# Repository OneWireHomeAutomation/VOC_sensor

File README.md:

# VOC_sensor
a one wire VOC sensor

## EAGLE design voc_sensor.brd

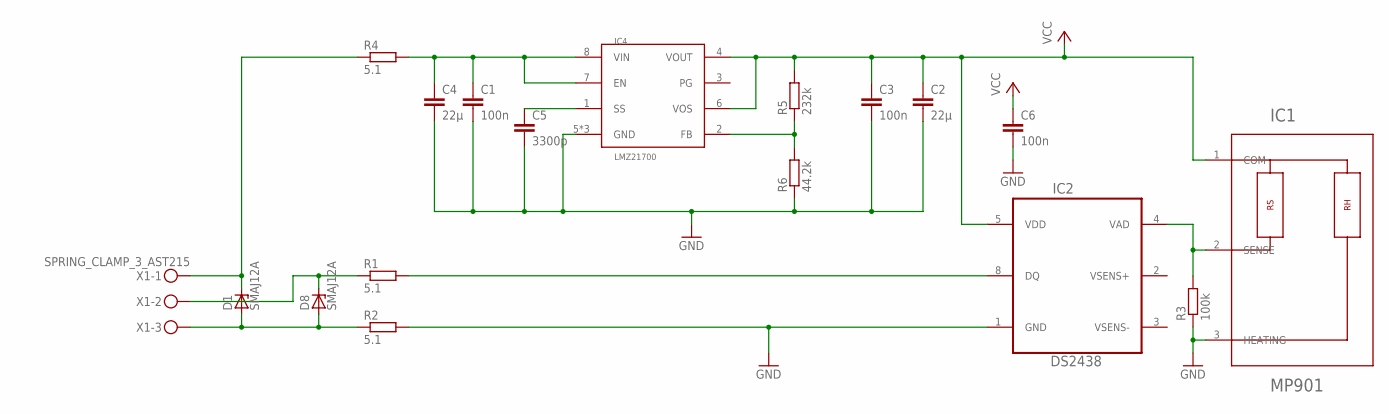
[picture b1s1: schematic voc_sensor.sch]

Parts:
C1: 100n; C0402; VOLTAGE >=25 V
C2: 22µ; C0805K; VOLTAGE >=6.3 V
C3, C6: 100n; C0402; VOLTAGE >=6.3 V
C4: 22µ; C0805K; VOLTAGE >=25 V
C5: 3300p; C0402; VOLTAGE >=25 V
D1, D8: SMAJ12A; DO214AC
IC1: MP901
IC2: DS2438; SO-08
IC4: LMZ21700
R1, R2, R4: 5.1; R0402
R3: 100k; R0402
R5: 232k; R0402
R6: 44.2k; R0402
X1: SPRING_CLAMP_3_AST215; AST215_3

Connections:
GND: C1.2, C2.2, C3.2, C4.2, C5.2, C6.2, IC1.3 (HEATING), IC2.1 (GND), IC4.5 (GND), IC4.TPAD@1 (GND), IC4.TPAD@2 (GND), R2.2, R3.1, R6.1
unnamed: IC1.2 (SENSE), IC2.4 (VAD), R3.2
unnamed: C1.1, C4.1, IC4.7 (EN), IC4.8 (VIN), R4.2
unnamed: D1.C, R4.1, X1.1A, X1.1B
unnamed: D1.A, D8.A, R2.1, X1.3A, X1.3B
unnamed: C5.1, IC4.1 (SS)
unnamed: IC4.2 (FB), R5.1, R6.2
unnamed: D8.C, R1.1, X1.2A, X1.2B
unnamed: IC2.8 (DQ), R1.2
VCC: C2.1, C3.1, C6.1, IC1.1 (COM), IC2.5 (VDD), IC4.4 (VOUT), IC4.6 (VOS), R5.2

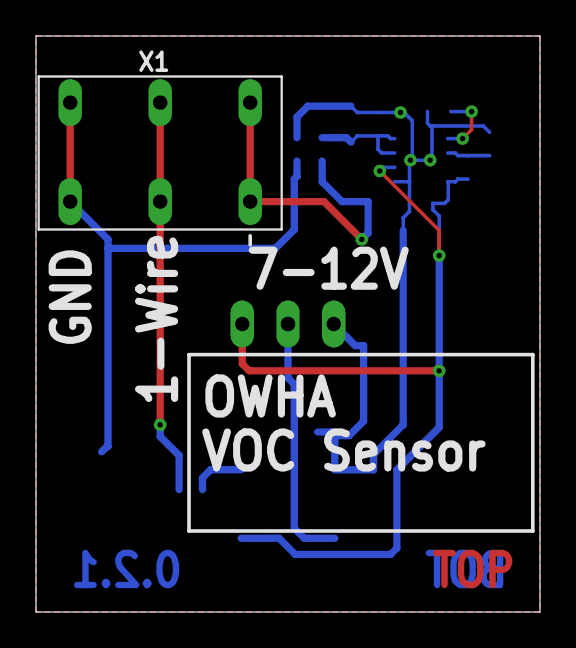
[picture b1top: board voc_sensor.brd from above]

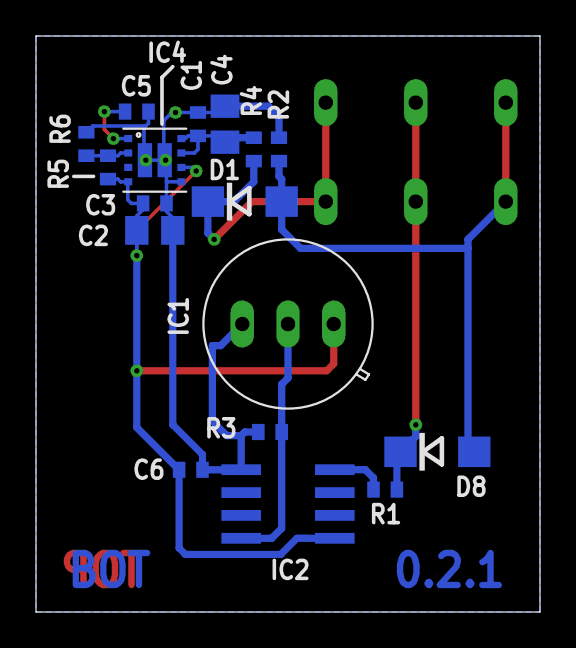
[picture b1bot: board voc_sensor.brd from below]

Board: 2 copper layers, 28.0 x 32.0 mm, 18 parts (17 on the bottom side), 10 nets.

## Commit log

2016-06-07 adding first test of sensor PCB and schematic
2016-06-10 changing some values: 5 Ohm resistor to 5.1 Ohm (5 Ohm is not broadly available) selected different type of TVS diode with essentially the same ratings
2016-06-26 changing load resistor to 100k as stated on the sensor packaging... already tried this and it works like a charm
2016-06-26 adding automatic testing and release
2016-06-26 changing filename of BOM file in release.sh zip command
2016-06-26 replaced connector X1 to get a lower profile inside of the wall insert (resolves issue #2)
2016-07-17 changing the 5V regulator to a switching type and adding some stuff to make the revision visible on the board without guesswork
2016-08-24 moving clamping terminal to get out of the way of case parts and removing some DRC errors
2016-08-24 making name and place layers pretty
2016-08-24 further improving the placement print
2016-08-24 changing PCB thickness
2016-10-02 adding voltage specifications to all capacitors solving issue #4
2016-10-02 changing D1 and D8 to 12V types, resulting in an increased voltage compared to previous versions of the schematic - but it lowers the expected voltage range, which was 7-17 V - now it is 7-12V relate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
2016-10-02 changing voltage spec on the PCB silkscreen
2016-10-02 setting >REVISION to 0.2.1
